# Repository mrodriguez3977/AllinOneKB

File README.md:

# AllinOneKB
First attempt at a 100% ortholinear keyboard with g keys

This keyboard uses an ATmega32U4 microprocessor, and the schematic is based on the PJRC Teensy at https://www.pjrc.com/store/teensy.html, The keyboard is designed to be an ortholinear keyboard, but with a few changes can also be turned into a regular keyboard. 
The keyboard supports both micro usb and usb-c.

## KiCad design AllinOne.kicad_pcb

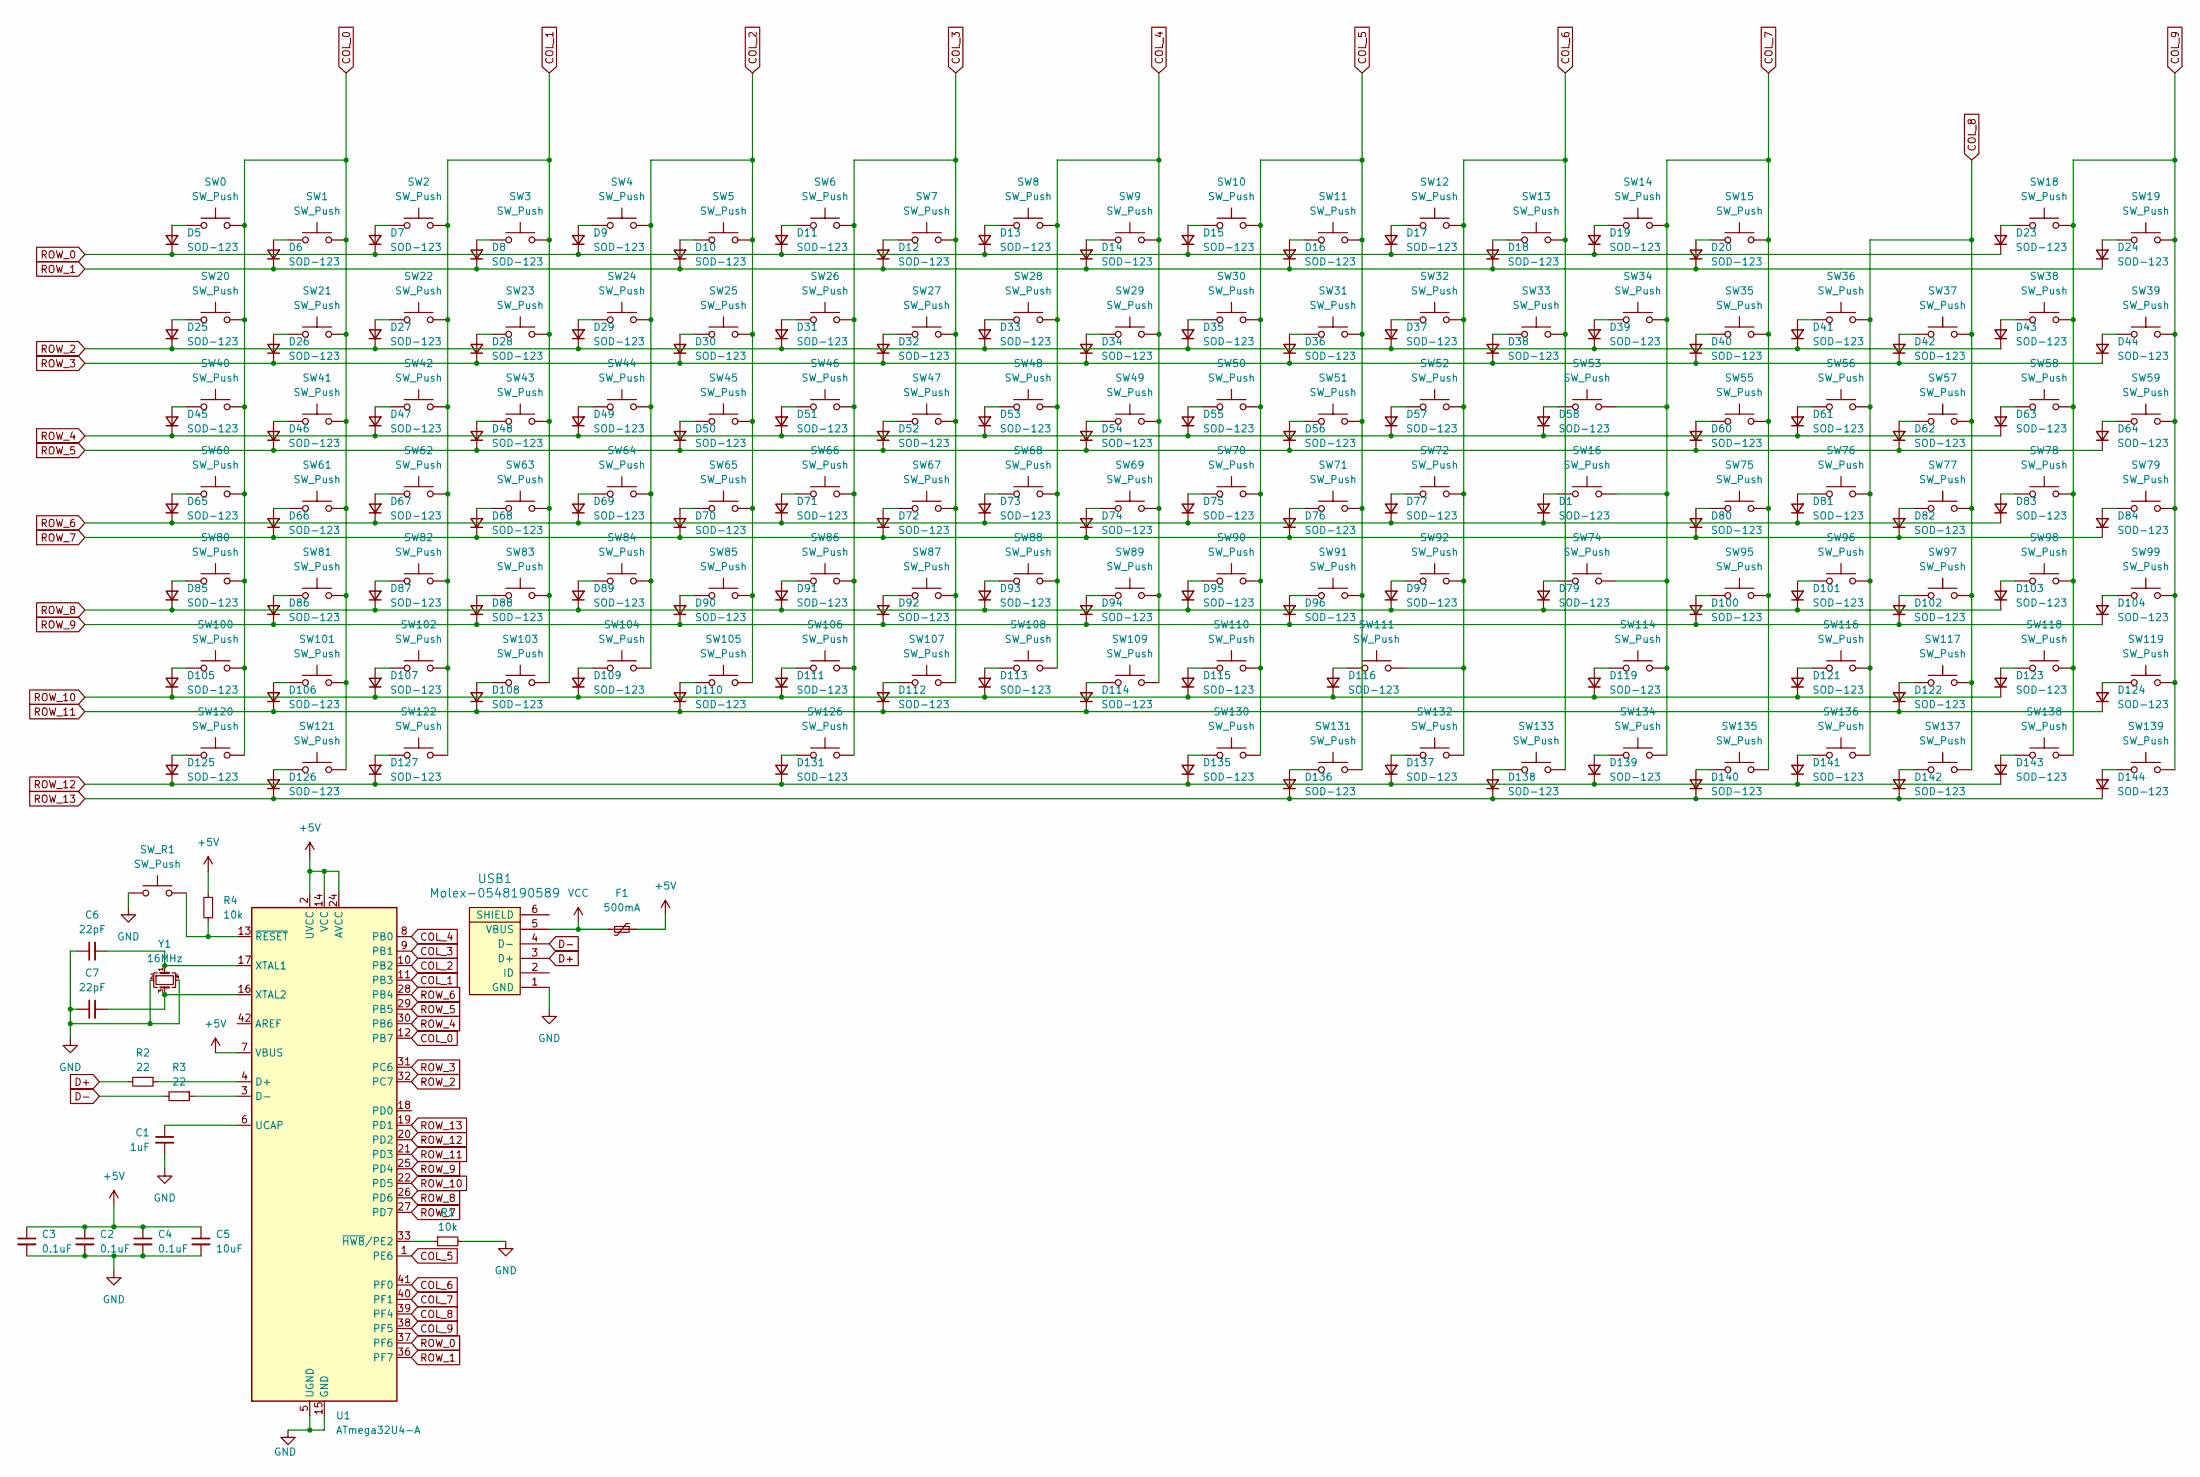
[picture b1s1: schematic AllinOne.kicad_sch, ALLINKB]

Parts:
C1: 1uF; C_0805_2012Metric
C2, C3, C4: 0.1uF; C_0805_2012Metric
C5: 10uF; C_0805_2012Metric
C6, C7: 22pF; C_0805_2012Metric
D1, D5, D6, D7, D8, D9, D10, D11, D12, D13, D14, D15, D16, D17, D18, D19, D20, D23, D24, D25, D26, D27, D28, D29, D30, D31, D32, D33, D34, D35, D36, D37, D38, D39, D40, D41, D42, D43, D44, D45, D46, D47, D48, D49, D50, D51, D52, D53, D54, D55, D56, D57, D58, D60, D61, D62, D63, D64, D65, D66, D67, D68, D69, D70, D71, D72, D73, D74, D75, D76, D77, D79, D80, D81, D82, D83, D84, D85, D86, D87, D88, D89, D90, D91, D92, D93, D94, D95, D96, D97, D100, D101, D102, D103, D104, D105, D106, D107, D108, D109, D110, D111, D112, D113, D114, D115, D116, D119, D121, D122, D123, D124, D125, D126, D127, D131, D135, D136, D137, D138, D139, D140, D141, D142, D143, D144: SOD-123; D_SOD-123
F1: 500mA; Fuse_1206_3216Metric
R1, R4: 10k; R_0805_2012Metric
R2, R3: 22; R_0805_2012Metric
SW0, SW1, SW2, SW3, SW4, SW5, SW6, SW7, SW8, SW9, SW10, SW11, SW12, SW13, SW14, SW15, SW18, SW19, SW20, SW21, SW22, SW23, SW24, SW25, SW26, SW27, SW28, SW29, SW30, SW31, SW32, SW33, SW34, SW35, SW36, SW37, SW38, SW39, SW40, SW41, SW42, SW43, SW44, SW45, SW46, SW47, SW48, SW49, SW50, SW51, SW52, SW55, SW56, SW57, SW58, SW59, SW60, SW61, SW62, SW63, SW64, SW65, SW66, SW67, SW68, SW69, SW70, SW71, SW72, SW75, SW76, SW77, SW78, SW79, SW80, SW81, SW82, SW83, SW84, SW85, SW86, SW87, SW88, SW89, SW90, SW91, SW92, SW95, SW96, SW97, SW98, SW99, SW100, SW101, SW102, SW103, SW104, SW105, SW106, SW107, SW108, SW109, SW110, SW114, SW116, SW117, SW118, SW119, SW120, SW121, SW122, SW130, SW131, SW132, SW133, SW134, SW135, SW136, SW137, SW138, SW139: SW_Push; SW_Cherry_MX_1.00u_PCB
SW16, SW53, SW74, SW111: SW_Push; SW_Cherry_MX_2.00u_PCB
SW126: SW_Push; SW_Cherry_MX_6.25u_PCB
SW_R1: SW_Push; SKQG-1155865
U1: ATmega32U4-A; TQFP-44_10x10mm_P0.8mm
USB1: Molex-0548190589
Y1: 16MHz; Crystal_SMD_3225-4Pin_3.2x2.5mm

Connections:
+5V: C2.1, C3.1, C4.1, C5.1, F1.1, R4.2, U1.2 (UVCC), U1.7 (VBUS), U1.14 (VCC), U1.24 (AVCC), U1.34 (VCC), U1.44 (AVCC)
COL_0: SW0.2, SW1.2, SW20.2, SW21.2, SW40.2, SW41.2, SW60.2, SW61.2, SW80.2, SW81.2, SW100.2, SW101.2, SW120.2, SW121.2, U1.12 (PB7)
COL_1: SW2.2, SW3.2, SW22.2, SW23.2, SW42.2, SW43.2, SW62.2, SW63.2, SW82.2, SW83.2, SW102.2, SW103.2, SW122.2, U1.11 (PB3)
COL_2: SW4.2, SW5.2, SW24.2, SW25.2, SW44.2, SW45.2, SW64.2, SW65.2, SW84.2, SW85.2, SW104.2, SW105.2, U1.10 (PB2)
COL_3: SW6.2, SW7.2, SW26.2, SW27.2, SW46.2, SW47.2, SW66.2, SW67.2, SW86.2, SW87.2, SW106.2, SW107.2, SW126.2, U1.9 (PB1)
COL_4: SW8.2, SW9.2, SW28.2, SW29.2, SW48.2, SW49.2, SW68.2, SW69.2, SW88.2, SW89.2, SW108.2, SW109.2, U1.8 (PB0)
COL_5: SW10.2, SW11.2, SW30.2, SW31.2, SW50.2, SW51.2, SW70.2, SW71.2, SW90.2, SW91.2, SW110.2, SW130.2, SW131.2, U1.1 (PE6)
COL_6: SW12.2, SW13.2, SW32.2, SW33.2, SW52.2, SW72.2, SW92.2, SW111.2, SW132.2, SW133.2, U1.41 (PF0)
COL_7: SW14.2, SW15.2, SW16.2, SW34.2, SW35.2, SW53.2, SW55.2, SW74.2, SW75.2, SW95.2, SW114.2, SW134.2, SW135.2, U1.40 (PF1)
COL_8: SW36.2, SW37.2, SW56.2, SW57.2, SW76.2, SW77.2, SW96.2, SW97.2, SW116.2, SW117.2, SW136.2, SW137.2, U1.39 (PF4)
COL_9: SW18.2, SW19.2, SW38.2, SW39.2, SW58.2, SW59.2, SW78.2, SW79.2, SW98.2, SW99.2, SW118.2, SW119.2, SW138.2, SW139.2, U1.38 (PF5)
D+: R2.2, USB1.3 (D+)
D-: R3.2, USB1.4 (D-)
GND: C1.2, C2.2, C3.2, C4.2, C5.2, C6.1, C7.1, R1.2, SW_R1.1, U1.5 (UGND), U1.15 (GND), U1.23 (GND), U1.35 (GND), U1.43 (GND), USB1.1 (GND), Y1.2, Y1.4
unnamed: D1.2 (A), SW16.1
unnamed: D5.2 (A), SW0.1
unnamed: D6.2 (A), SW1.1
unnamed: D7.2 (A), SW2.1
unnamed: D8.2 (A), SW3.1
unnamed: D9.2 (A), SW4.1
unnamed: D10.2 (A), SW5.1
unnamed: D11.2 (A), SW6.1
unnamed: D12.2 (A), SW7.1
unnamed: D13.2 (A), SW8.1
unnamed: D14.2 (A), SW9.1
unnamed: D15.2 (A), SW10.1
unnamed: D16.2 (A), SW11.1
unnamed: D17.2 (A), SW12.1
unnamed: D18.2 (A), SW13.1
unnamed: D19.2 (A), SW14.1
unnamed: D20.2 (A), SW15.1
unnamed: D23.2 (A), SW18.1
unnamed: D24.2 (A), SW19.1
unnamed: D25.2 (A), SW20.1
unnamed: D26.2 (A), SW21.1
unnamed: D27.2 (A), SW22.1
unnamed: D28.2 (A), SW23.1
unnamed: D29.2 (A), SW24.1
unnamed: D30.2 (A), SW25.1
unnamed: D31.2 (A), SW26.1
unnamed: D32.2 (A), SW27.1
unnamed: D33.2 (A), SW28.1
unnamed: D34.2 (A), SW29.1
unnamed: D35.2 (A), SW30.1
unnamed: D36.2 (A), SW31.1
unnamed: D37.2 (A), SW32.1
unnamed: D38.2 (A), SW33.1
unnamed: D39.2 (A), SW34.1
unnamed: D40.2 (A), SW35.1
unnamed: D41.2 (A), SW36.1
unnamed: D42.2 (A), SW37.1
unnamed: D43.2 (A), SW38.1
unnamed: D44.2 (A), SW39.1
unnamed: D45.2 (A), SW40.1
unnamed: D46.2 (A), SW41.1
unnamed: D47.2 (A), SW42.1
unnamed: D48.2 (A), SW43.1
unnamed: D49.2 (A), SW44.1
unnamed: D50.2 (A), SW45.1
unnamed: D51.2 (A), SW46.1
unnamed: D52.2 (A), SW47.1
unnamed: D53.2 (A), SW48.1
unnamed: D54.2 (A), SW49.1
unnamed: D55.2 (A), SW50.1
unnamed: D56.2 (A), SW51.1
unnamed: D57.2 (A), SW52.1
unnamed: D58.2 (A), SW53.1
unnamed: D60.2 (A), SW55.1
unnamed: D61.2 (A), SW56.1
unnamed: D62.2 (A), SW57.1
unnamed: D63.2 (A), SW58.1
unnamed: D64.2 (A), SW59.1
unnamed: D65.2 (A), SW60.1
unnamed: D66.2 (A), SW61.1
unnamed: D67.2 (A), SW62.1
unnamed: D68.2 (A), SW63.1
unnamed: D69.2 (A), SW64.1
unnamed: D70.2 (A), SW65.1
unnamed: D71.2 (A), SW66.1
unnamed: D72.2 (A), SW67.1
unnamed: D73.2 (A), SW68.1
unnamed: D74.2 (A), SW69.1
unnamed: D75.2 (A), SW70.1
unnamed: D76.2 (A), SW71.1
unnamed: D77.2 (A), SW72.1
unnamed: D79.2 (A), SW74.1
unnamed: D80.2 (A), SW75.1
unnamed: D81.2 (A), SW76.1
unnamed: D82.2 (A), SW77.1
unnamed: D83.2 (A), SW78.1
unnamed: D84.2 (A), SW79.1
unnamed: D85.2 (A), SW80.1
unnamed: D86.2 (A), SW81.1
unnamed: D87.2 (A), SW82.1
unnamed: D88.2 (A), SW83.1
unnamed: D89.2 (A), SW84.1
unnamed: D90.2 (A), SW85.1
unnamed: D91.2 (A), SW86.1
unnamed: D92.2 (A), SW87.1
unnamed: D93.2 (A), SW88.1
unnamed: D94.2 (A), SW89.1
unnamed: D95.2 (A), SW90.1
unnamed: D96.2 (A), SW91.1
unnamed: D97.2 (A), SW92.1
unnamed: D100.2 (A), SW95.1
unnamed: D101.2 (A), SW96.1
unnamed: D102.2 (A), SW97.1
unnamed: D103.2 (A), SW98.1
unnamed: D104.2 (A), SW99.1
unnamed: D105.2 (A), SW100.1
unnamed: D106.2 (A), SW101.1
unnamed: D107.2 (A), SW102.1
unnamed: D108.2 (A), SW103.1
unnamed: D109.2 (A), SW104.1
unnamed: D110.2 (A), SW105.1
unnamed: D111.2 (A), SW106.1
unnamed: D112.2 (A), SW107.1
unnamed: D113.2 (A), SW108.1
unnamed: D114.2 (A), SW109.1
unnamed: D115.2 (A), SW110.1
unnamed: D116.2 (A), SW111.1
unnamed: D119.2 (A), SW114.1
unnamed: D121.2 (A), SW116.1
unnamed: D122.2 (A), SW117.1
unnamed: D123.2 (A), SW118.1
unnamed: D124.2 (A), SW119.1
unnamed: D125.2 (A), SW120.1
unnamed: D126.2 (A), SW121.1
unnamed: D127.2 (A), SW122.1
unnamed: D131.2 (A), SW126.1
unnamed: D135.2 (A), SW130.1
unnamed: D136.2 (A), SW131.1
unnamed: D137.2 (A), SW132.1
unnamed: D138.2 (A), SW133.1
unnamed: D139.2 (A), SW134.1
unnamed: D140.2 (A), SW135.1
unnamed: D141.2 (A), SW136.1
unnamed: D142.2 (A), SW137.1
unnamed: D143.2 (A), SW138.1
unnamed: D144.2 (A), SW139.1
unnamed: R2.1, U1.4 (D+)
unnamed: R3.1, U1.3 (D-)
unnamed: C1.1, U1.6 (UCAP)
unnamed: C6.2, U1.17 (XTAL1), Y1.1
unnamed: C7.2, U1.16 (XTAL2), Y1.3
unnamed: R1.1, U1.33 (~HWB/PE2)
unnamed: R4.1, SW_R1.2, U1.13 (~RESET)
ROW_0: D5.1 (K), D7.1 (K), D9.1 (K), D11.1 (K), D13.1 (K), D15.1 (K), D17.1 (K), D19.1 (K), D23.1 (K), U1.37 (PF6)
ROW_1: D6.1 (K), D8.1 (K), D10.1 (K), D12.1 (K), D14.1 (K), D16.1 (K), D18.1 (K), D20.1 (K), D24.1 (K), U1.36 (PF7)
ROW_2: D25.1 (K), D27.1 (K), D29.1 (K), D31.1 (K), D33.1 (K), D35.1 (K), D37.1 (K), D39.1 (K), D41.1 (K), D43.1 (K), U1.32 (PC7)
ROW_3: D26.1 (K), D28.1 (K), D30.1 (K), D32.1 (K), D34.1 (K), D36.1 (K), D38.1 (K), D40.1 (K), D42.1 (K), D44.1 (K), U1.31 (PC6)
ROW_4: D45.1 (K), D47.1 (K), D49.1 (K), D51.1 (K), D53.1 (K), D55.1 (K), D57.1 (K), D58.1 (K), D61.1 (K), D63.1 (K), U1.30 (PB6)
ROW_5: D46.1 (K), D48.1 (K), D50.1 (K), D52.1 (K), D54.1 (K), D56.1 (K), D60.1 (K), D62.1 (K), D64.1 (K), U1.29 (PB5)
ROW_6: D1.1 (K), D65.1 (K), D67.1 (K), D69.1 (K), D71.1 (K), D73.1 (K), D75.1 (K), D77.1 (K), D81.1 (K), D83.1 (K), U1.28 (PB4)
ROW_7: D66.1 (K), D68.1 (K), D70.1 (K), D72.1 (K), D74.1 (K), D76.1 (K), D80.1 (K), D82.1 (K), D84.1 (K), U1.27 (PD7)
ROW_8: D79.1 (K), D85.1 (K), D87.1 (K), D89.1 (K), D91.1 (K), D93.1 (K), D95.1 (K), D97.1 (K), D101.1 (K), D103.1 (K), U1.26 (PD6)
ROW_9: D86.1 (K), D88.1 (K), D90.1 (K), D92.1 (K), D94.1 (K), D96.1 (K), D100.1 (K), D102.1 (K), D104.1 (K), U1.25 (PD4)
ROW_10: D105.1 (K), D107.1 (K), D109.1 (K), D111.1 (K), D113.1 (K), D115.1 (K), D116.1 (K), D119.1 (K), D121.1 (K), D123.1 (K), U1.22 (PD5)
ROW_11: D106.1 (K), D108.1 (K), D110.1 (K), D112.1 (K), D114.1 (K), D122.1 (K), D124.1 (K), U1.21 (PD3)
ROW_12: D125.1 (K), D127.1 (K), D131.1 (K), D135.1 (K), D137.1 (K), D139.1 (K), D141.1 (K), D143.1 (K), U1.20 (PD2)
ROW_13: D126.1 (K), D136.1 (K), D138.1 (K), D140.1 (K), D142.1 (K), D144.1 (K), U1.19 (PD1)
VCC: F1.2, USB1.5 (VBUS)

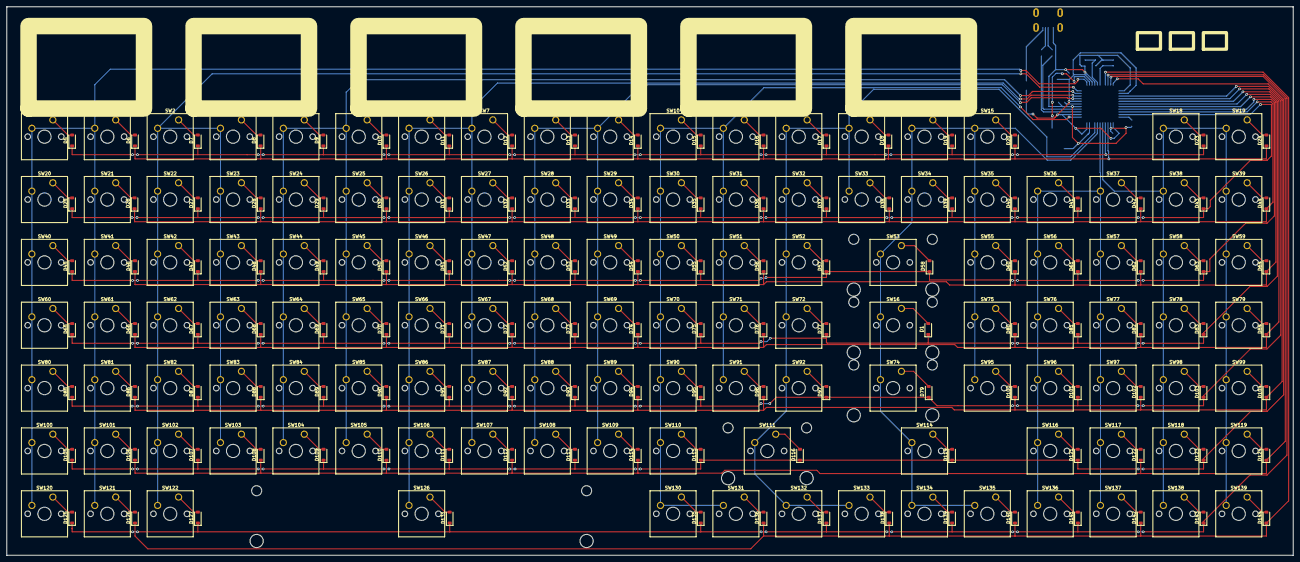
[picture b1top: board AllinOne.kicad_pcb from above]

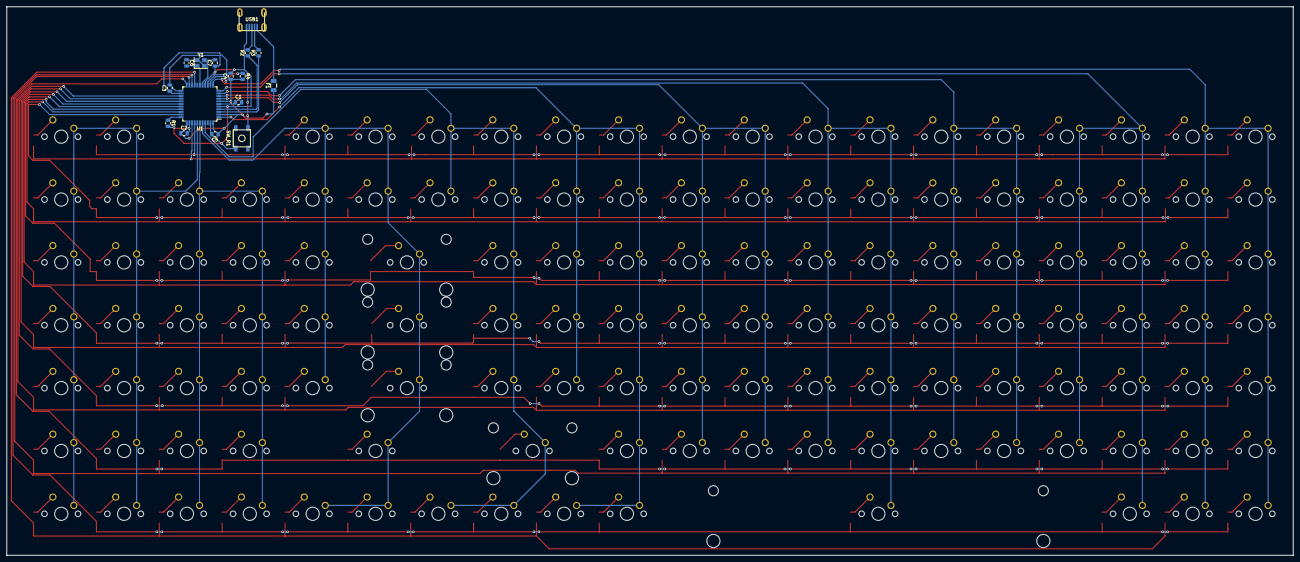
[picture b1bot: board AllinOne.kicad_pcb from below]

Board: 2 copper layers, 389.9 x 166.2 mm, 268 parts (16 on the bottom side), 162 nets.

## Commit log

2023-07-12 Initial Setup
    Just adding the basic files
2023-07-13 MCU set up finished
2023-07-13 Schematic all done
2023-07-27 Wired MCU
    Wired the 32U4 and updated the schematic just needs to add all switches
2023-09-16 Started organizing switches
2023-09-16 Finished switch lineup
2023-09-17 Started diode placement
2023-09-17 Finished one row of diodes
2023-09-19 Halfway done with diodes
2023-09-19 Finished now just wire
2023-09-19 Started routing the rows and finished the columns
2023-09-19 almost done wiring all rows
2023-09-20 Finished wiring rows and columns just needs MCU
2023-09-20 Started routing to MCU
2023-09-21 Almost done wiring to the mcu
2023-09-21 All Done for now
